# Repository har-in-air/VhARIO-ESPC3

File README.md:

# VhARIO-ESPC3 Rev B

Kicad 6 circuit schematic and PCB layout for an audio variometer using ESP32-C3 and CJMCU-117 IMU modules. The vario uses a Kalman filter to fuse acceleration data and pressure altitude data for 'zero-lag' response. You can find the [firmware project here](https://github.com/har-in-air/ESP32C3_BLUETOOTH_AUDIO_VARIO).

2-layer PCB sized for [Hammond 1551K 80x40x20 mm enclosure](docs/1551K.pdf).

Li-poly battery recharging via USB-C.

ESP32-C3 flash and debug via built-in USB serial jtag peripheral.

All SMD passive components use Kicad hand-solderable footprints.

All component symbols and footprints used in the project are in project-specific libraries in the `/libraries` folder.

## Hardware

* AI-Thinker  ESP-C3 12F module (C3FN4) with 4MByte flash.
* CJMCU-117 IMU module (MPU9250 + MS5611).
* 74HC240 used as push-pull piezo speaker driver.
* 1800mAH Li-Poly battery.
* MCP73871 battery charger @ 500mA max.
* Soft-switched power on/off via SW3.
* USB serial jtag programming and debug via USB-C interface. The flash/debug jumper can be a PCM12 slide switch (SW2) on the bottom layer if you want access from outside the enclosure. Or you can solder a 2.54mm pitch header with a jumper cap (JP1) on the top layer. The jumper is shorted only for flash/debug and is open for normal vario operation.

## Schematic
[Schematic PDF](docs/vhario-espc3-schematic.pdf)

## Differences between Rev A and Rev B hardware
* The Rev A archive can be found in the releases section.
* Rev B is a Kicad 6 project (6.0.6 as of date). Rev A was unfortunately developed with the Kicad 6.99 development branch. This is incompatible with the Kicad 6 project file format. The Rev A project can only be opened with a Kicad 6.99 development build from 2022 Jan 26 or later.
* Flash and debug in Rev B uses the ESP32-C3 built-in USB serial jtag peripheral with a jumper or slide switch (JP1/SW2). For Rev A hardware, an external USB-UART adapter and jumper/switch is required. 
* For Rev B, all smd components except for a couple of modules have been placed on one side of the PCB to facilitate automated assembly.
* For Rev B, the power/bluetooth LED and charging status LED are placed together so only one enclosure LED window is required.
* The [firmware](https://github.com/har-in-air/ESP32C3_BLUETOOTH_AUDIO_VARIO) can be configured to support either Rev A or Rev B hardware. The configuration options are in the `platformio.ini` file.

## Kicad 3D view

## Assembly

# Credits

Prototype design, component sourcing and PCB assembly in collaboration with Benoit Arnal.

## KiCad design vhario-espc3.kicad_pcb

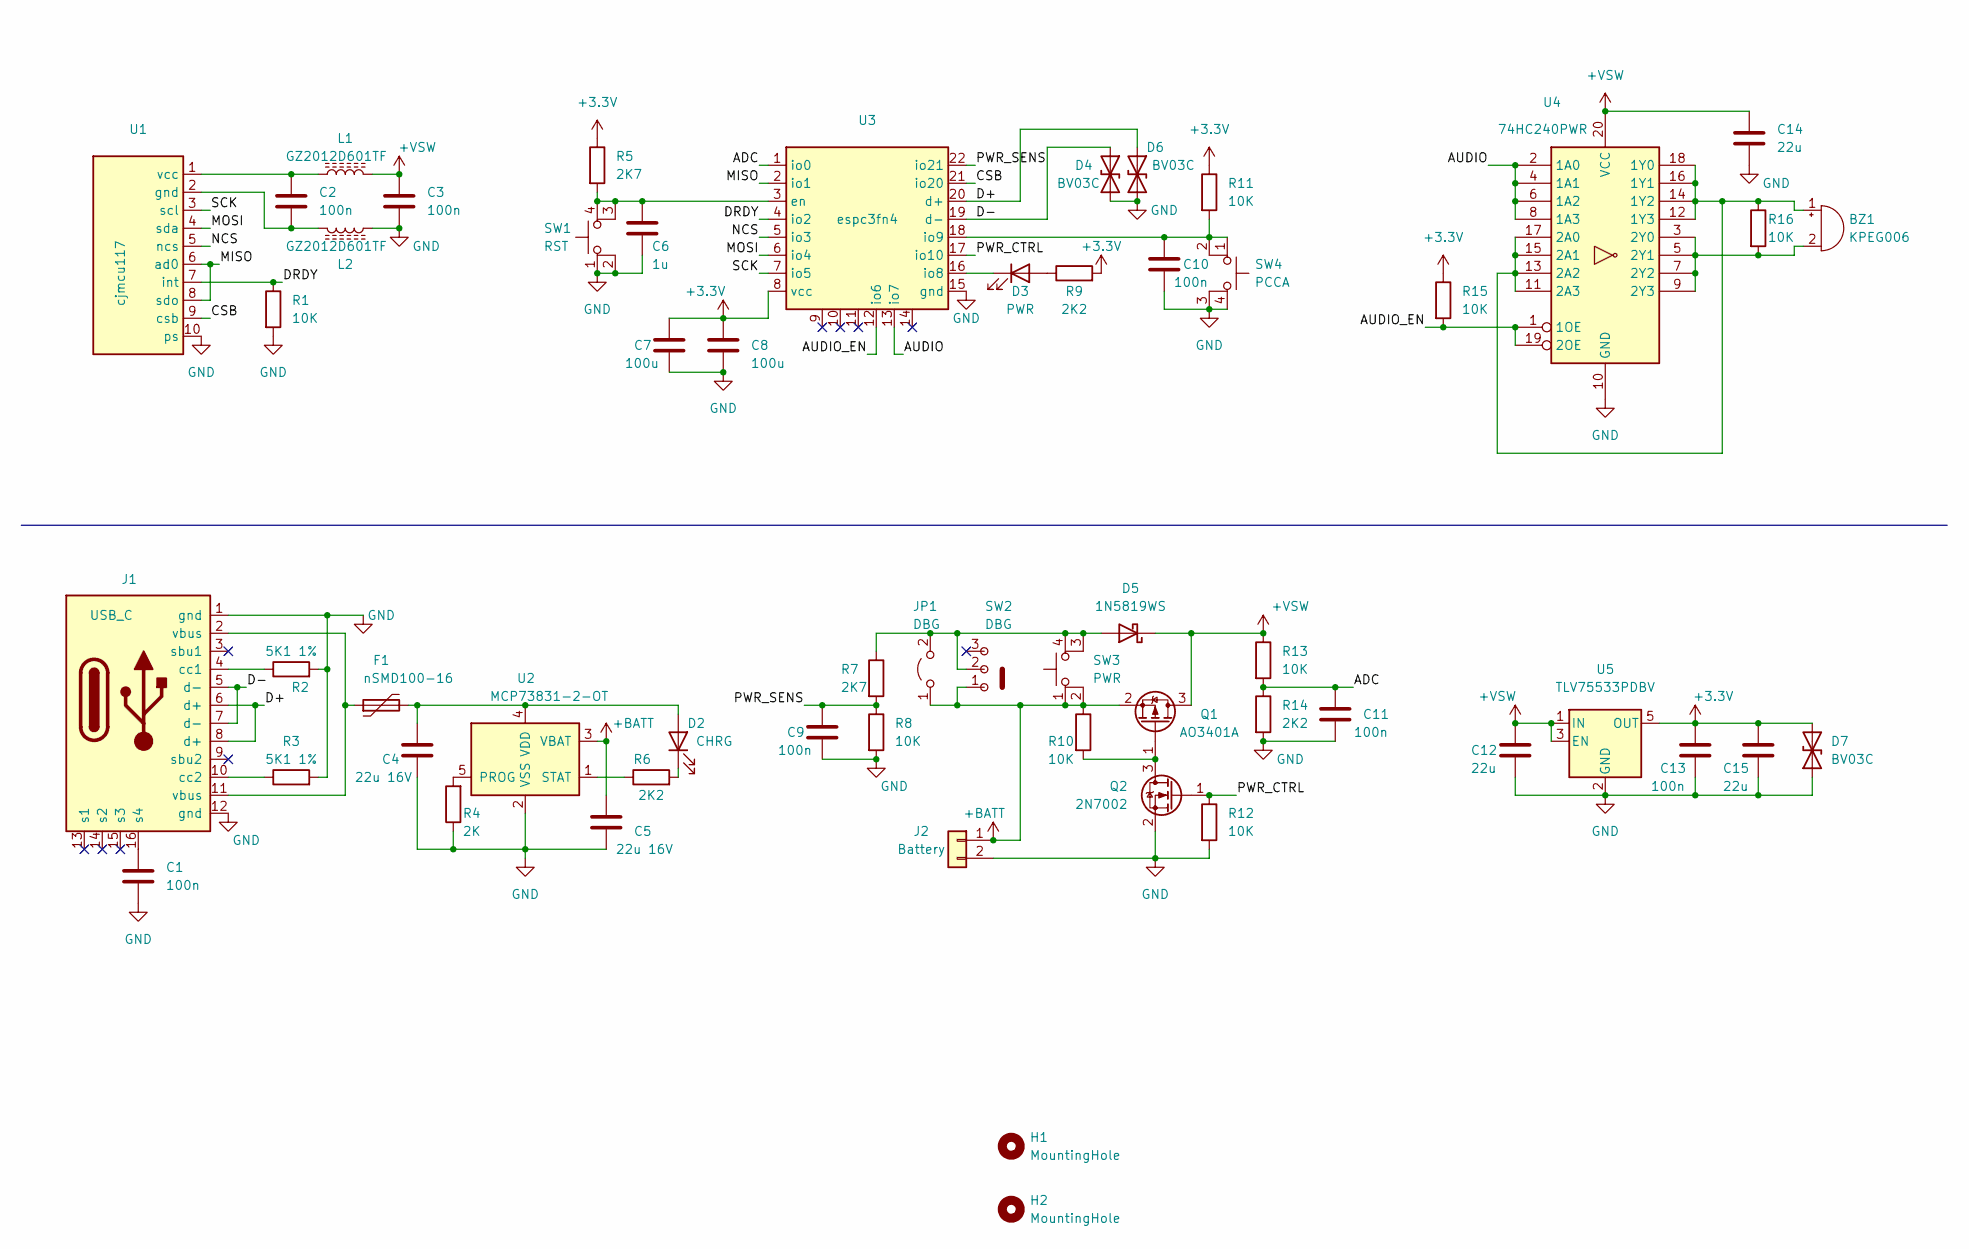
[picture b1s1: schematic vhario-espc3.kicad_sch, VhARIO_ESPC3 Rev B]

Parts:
BZ1: KPEG006; conn_smd_1x2_2mm
C1, C2, C3, C9, C10, C11, C13: 100n; C_0603_1608Metric_Pad1.08x0.95mm_HandSolder
C4, C5: 22u 16V; C_1206_3216Metric_Pad1.33x1.80mm_HandSolder
C6: 1u; C_0603_1608Metric_Pad1.08x0.95mm_HandSolder
C7, C8: 100u; C_1206_3216Metric_Pad1.33x1.80mm_HandSolder
C12, C14, C15: 22u; C_1206_3216Metric_Pad1.33x1.80mm_HandSolder
D2: CHRG; LED_0805_2012Metric_Pad1.15x1.40mm_HandSolder
D3: PWR; LED_0805_2012Metric_Pad1.15x1.40mm_HandSolder
D4, D6, D7: BV03C; D_SOD-323_HandSoldering
D5: 1N5819WS; D_SOD-323_HandSoldering
F1: nSMD100-16; Fuse_1812_4532Metric_Pad1.30x3.40mm_HandSolder
H1, H2: MountingHole; MountingHole_2.5mm
J1: USB_C; usb_c_16
J2: Battery; JST_PH_B2B-PH-K_1x02_P2.00mm_Vertical
JP1: DBG; PinSocket_1x02_P2.54mm_Vertical
L1, L2: GZ2012D601TF; L_0805_2012Metric_Pad1.15x1.40mm_HandSolder
Q1: AO3401A; SOT-23
Q2: 2N7002; SOT-23
R1, R8, R10, R11, R12, R13, R15, R16: 10K; R_0603_1608Metric_Pad0.98x0.95mm_HandSolder
R2, R3: 5K1 1%; R_0603_1608Metric_Pad0.98x0.95mm_HandSolder
R4: 2K; R_0603_1608Metric_Pad0.98x0.95mm_HandSolder
R5, R7: 2K7; R_0603_1608Metric_Pad0.98x0.95mm_HandSolder
R6: 2K2; C_0603_1608Metric_Pad1.08x0.95mm_HandSolder
R9, R14: 2K2; R_0603_1608Metric_Pad0.98x0.95mm_HandSolder
SW1: RST; smd_btn4
SW2: DBG; SW_SPDT_PCM12
SW3: PWR; smd_btn4
SW4: PCCA; smd_btn4
U1: cjmcu117
U2: MCP73831-2-OT; SOT-23-5
U3: espc3fn4
U4: 74HC240PWR; SSOP-20_4.4x6.5mm_P0.65mm
U5: TLV75533PDBV; SOT-23-5

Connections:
+3V3: C7.1, C8.1, C13.1, C15.1, D7.2 (A2), R5.1, R9.2, R11.1, R15.1, U3.8 (vcc), U5.5 (OUT)
+BATT: C5.1, J2.1, JP1.1 (A), Q1.2 (S), R10.1, SW2.1 (A), SW3.1, SW3.2, U2.3 (VBAT); also elsewhere on the board
+VSW: C3.1, C12.1, C14.1, D5.1 (K), L1.2, Q1.3 (D), R13.1, U4.20 (VCC), U5.1 (IN), U5.3 (EN)
/ADC: C11.1, R13.2, R14.1, U3.1 (io0)
/AUDIO: U3.13 (io7), U4.2 (1A0), U4.4 (1A1), U4.6 (1A2), U4.8 (1A3)
/AUDIO_EN: R15.2, U3.12 (io6), U4.1 (1OE), U4.19 (2OE)
/CSB: U1.9 (csb), U3.21 (io20)
/D+: D6.1 (A1), J1.6 (d+), J1.8 (d+), U3.20 (d+)
/D-: D4.1 (A1), J1.5 (d-), J1.7 (d-), U3.19 (d-)
/DRDY: R1.1, U1.7 (int), U3.4 (io2)
/MISO: U1.6 (ad0), U1.8 (sdo), U3.2 (io1)
/MOSI: U1.4 (sda), U3.6 (io4)
/NCS: U1.5 (ncs), U3.5 (io3)
/PWR_CTRL: Q2.1 (G), R12.1, U3.17 (io10)
/PWR_SENS: C9.1, R7.2, R8.1, U3.22 (io21)
/SCK: U1.3 (scl), U3.7 (io5)
GND: C1.2, C3.2, C4.2, C5.2, C6.2, C7.2, C8.2, C9.2, C10.2, C11.2, C12.2, C13.2, C14.2, C15.2, D4.2 (A2), D6.2 (A2), D7.1 (A1), J1.1 (gnd), J1.12 (gnd), J2.2, L2.1, Q2.2 (S), R1.2, R2.2, R3.2, R4.1, R8.2, R12.2, R14.2, SW1.1, SW1.2, SW4.3 (K), SW4.4 (A), U1.10 (ps), U2.2 (VSS), U3.15 (gnd), U4.10 (GND), U5.2 (GND); also elsewhere on the board
unnamed: BZ1.1 (-), R16.1, U4.11 (2A3), U4.12 (1Y3), U4.13 (2A2), U4.14 (1Y2), U4.15 (2A1), U4.16 (1Y1), U4.17 (2A0), U4.18 (1Y0)
unnamed: BZ1.2 (+), R16.2, U4.3 (2Y0), U4.5 (2Y1), U4.7 (2Y2), U4.9 (2Y3)
unnamed: C1.1, J1.16 (s4)
unnamed: C2.1, L1.1, U1.1 (vcc)
unnamed: C2.2, L2.2, U1.2 (gnd)
unnamed: C4.1, D2.2 (A), F1.2, U2.4 (VDD)
unnamed 23: C6.1, R5.2, SW1.3 (K), SW1.4 (A), U3.3 (en); also elsewhere on the board
unnamed 24: C10.1, R11.2, SW4.1, SW4.2, U3.18 (io9); also elsewhere on the board
unnamed: D2.1 (K), R6.2
unnamed: D3.1 (K), U3.16 (io8)
unnamed: D3.2 (A), R9.1
unnamed 28: D5.2 (A), JP1.2 (B), R7.1, SW2.2 (B), SW3.3 (K), SW3.4 (A); also elsewhere on the board
unnamed: F1.1, J1.2 (vbus), J1.11 (vbus)
unnamed: J1.4 (cc1), R2.1
unnamed: J1.10 (cc2), R3.1
unnamed: Q1.1 (G), Q2.3 (D), R10.2
unnamed: R4.2, U2.5 (PROG)
unnamed: R6.1, U2.1 (STAT)

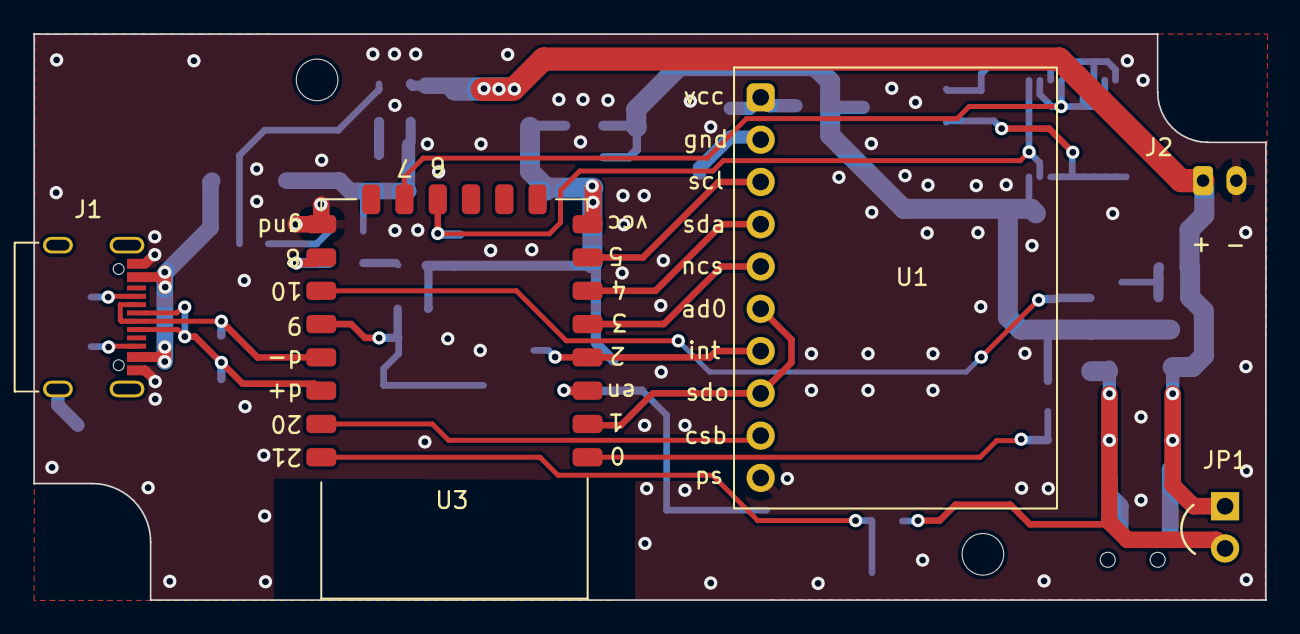
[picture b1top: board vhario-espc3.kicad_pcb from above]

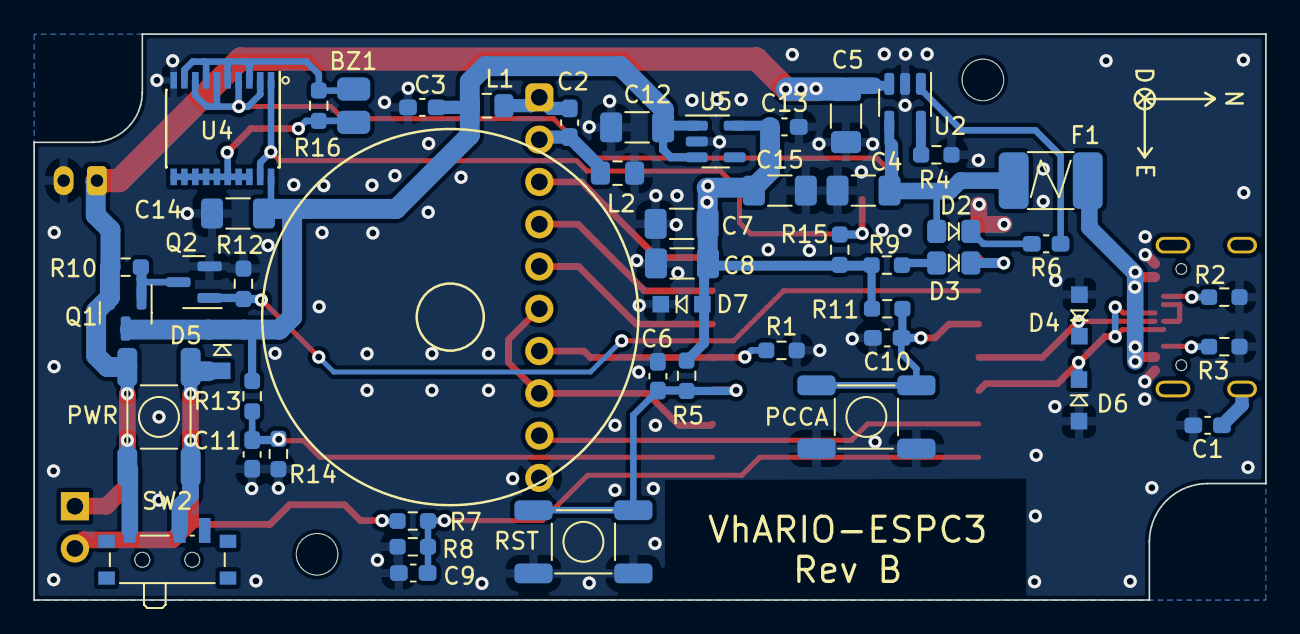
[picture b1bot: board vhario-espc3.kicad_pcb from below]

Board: 2 copper layers, 74.0 x 34.0 mm, 57 parts (50 on the bottom side), 35 nets.

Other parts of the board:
PCCA: PCCA; smd_btn4
PWR: PWR; smd_btn4
RST: RST; smd_btn4

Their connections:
+BATT: PWR.1, PWR.2; also elsewhere on the board
GND: PCCA.3 (K), PCCA.4 (A), RST.1, RST.2; also elsewhere on the board
unnamed 23: RST.3 (K), RST.4 (A); also elsewhere on the board
unnamed 24: PCCA.1, PCCA.2; also elsewhere on the board
unnamed 28: PWR.3 (K), PWR.4 (A); also elsewhere on the board

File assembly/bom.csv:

Designator,Footprint,Quantity,Value,LCSC Part #
H2,MountingHole_2.5mm,1,MountingHole,
U1,cjmcu117,1,cjmcu117,
H1,MountingHole_2.5mm,1,MountingHole,
J1,usb_c_16,1,USB_C,
U3,espc3fn4,1,espc3fn4,
J2,JST_PH_B2B-PH-K_1x02_P2.00mm_Vertical,1,Battery,
JP1,PinSocket_1x02_P2.54mm_Vertical,1,DBG,
F1,Fuse_1812_4532Metric_Pad1.30x3.40mm_HandSolder,1,nSMD100-16,
D6,D_SOD-323_HandSoldering,1,BV03C,
D4,D_SOD-323_HandSoldering,1,BV03C,
C1,C_0603_1608Metric_Pad1.08x0.95mm_HandSolder,1,100n,
R11,R_0603_1608Metric_Pad0.98x0.95mm_HandSolder,1,10K,
Q2,SOT-23,1,2N7002,
R5,R_0603_1608Metric_Pad0.98x0.95mm_HandSolder,1,2K7,
SW2,SW_SPDT_PCM12,1,DBG,
L2,L_0805_2012Metric_Pad1.15x1.40mm_HandSolder,1,GZ2012D601TF,
D2,LED_0805_2012Metric_Pad1.15x1.40mm_HandSolder,1,CHRG,
BZ1,conn_smd_1x2_2mm,1,KPEG006,
C12,C_1206_3216Metric_Pad1.33x1.80mm_HandSolder,1,22u,
C13,C_0603_1608Metric_Pad1.08x0.95mm_HandSolder,1,100n,
R2,R_0603_1608Metric_Pad0.98x0.95mm_HandSolder,1,5K1 1%,
C15,C_1206_3216Metric_Pad1.33x1.80mm_HandSolder,1,22u,
U2,SOT-23-5,1,MCP73831-2-OT,
R16,R_0603_1608Metric_Pad0.98x0.95mm_HandSolder,1,10K,
L1,L_0805_2012Metric_Pad1.15x1.40mm_HandSolder,1,GZ2012D601TF,
C3,C_0603_1608Metric_Pad1.08x0.95mm_HandSolder,1,100n,
U5,SOT-23-5,1,TLV75533PDBV,
C6,C_0603_1608Metric_Pad1.08x0.95mm_HandSolder,1,1u,
PWR,smd_btn4,1,PWR,
C2,C_0603_1608Metric_Pad1.08x0.95mm_HandSolder,1,100n,
PCCA,smd_btn4,1,PCCA,
R8,R_0603_1608Metric_Pad0.98x0.95mm_HandSolder,1,10K,
RST,smd_btn4,1,RST,
R12,R_0603_1608Metric_Pad0.98x0.95mm_HandSolder,1,10K,
R14,R_0603_1608Metric_Pad0.98x0.95mm_HandSolder,1,2K2,
R1,R_0603_1608Metric_Pad0.98x0.95mm_HandSolder,1,10K,
D5,D_SOD-323_HandSoldering,1,1N5819WS,
C4,C_1206_3216Metric_Pad1.33x1.80mm_HandSolder,1,22u 16V,
C11,C_0603_1608Metric_Pad1.08x0.95mm_HandSolder,1,100n,
R6,C_0603_1608Metric_Pad1.08x0.95mm_HandSolder,1,2K2,
R4,R_0603_1608Metric_Pad0.98x0.95mm_HandSolder,1,2K,
R3,R_0603_1608Metric_Pad0.98x0.95mm_HandSolder,1,5K1 1%,
R15,R_0603_1608Metric_Pad0.98x0.95mm_HandSolder,1,10K,
D7,D_SOD-323_HandSoldering,1,BV03C,
C5,C_1206_3216Metric_Pad1.33x1.80mm_HandSolder,1,22u 16V,
Q1,SOT-23,1,AO3401A,
R9,R_0603_1608Metric_Pad0.98x0.95mm_HandSolder,1,2K2,
D3,LED_0805_2012Metric_Pad1.15x1.40mm_HandSolder,1,PWR,
C10,C_0603_1608Metric_Pad1.08x0.95mm_HandSolder,1,100n,
R10,R_0603_1608Metric_Pad0.98x0.95mm_HandSolder,1,10K,
R7,R_0603_1608Metric_Pad0.98x0.95mm_HandSolder,1,2K7,
C14,C_1206_3216Metric_Pad1.33x1.80mm_HandSolder,1,22u,
C8,C_1206_3216Metric_Pad1.33x1.80mm_HandSolder,1,100u,
C7,C_1206_3216Metric_Pad1.33x1.80mm_HandSolder,1,100u,
R13,R_0603_1608Metric_Pad0.98x0.95mm_HandSolder,1,10K,
U4,SSOP-20_4.4x6.5mm_P0.65mm,1,74HC240PWR,
C9,C_0603_1608Metric_Pad1.08x0.95mm_HandSolder,1,100n,

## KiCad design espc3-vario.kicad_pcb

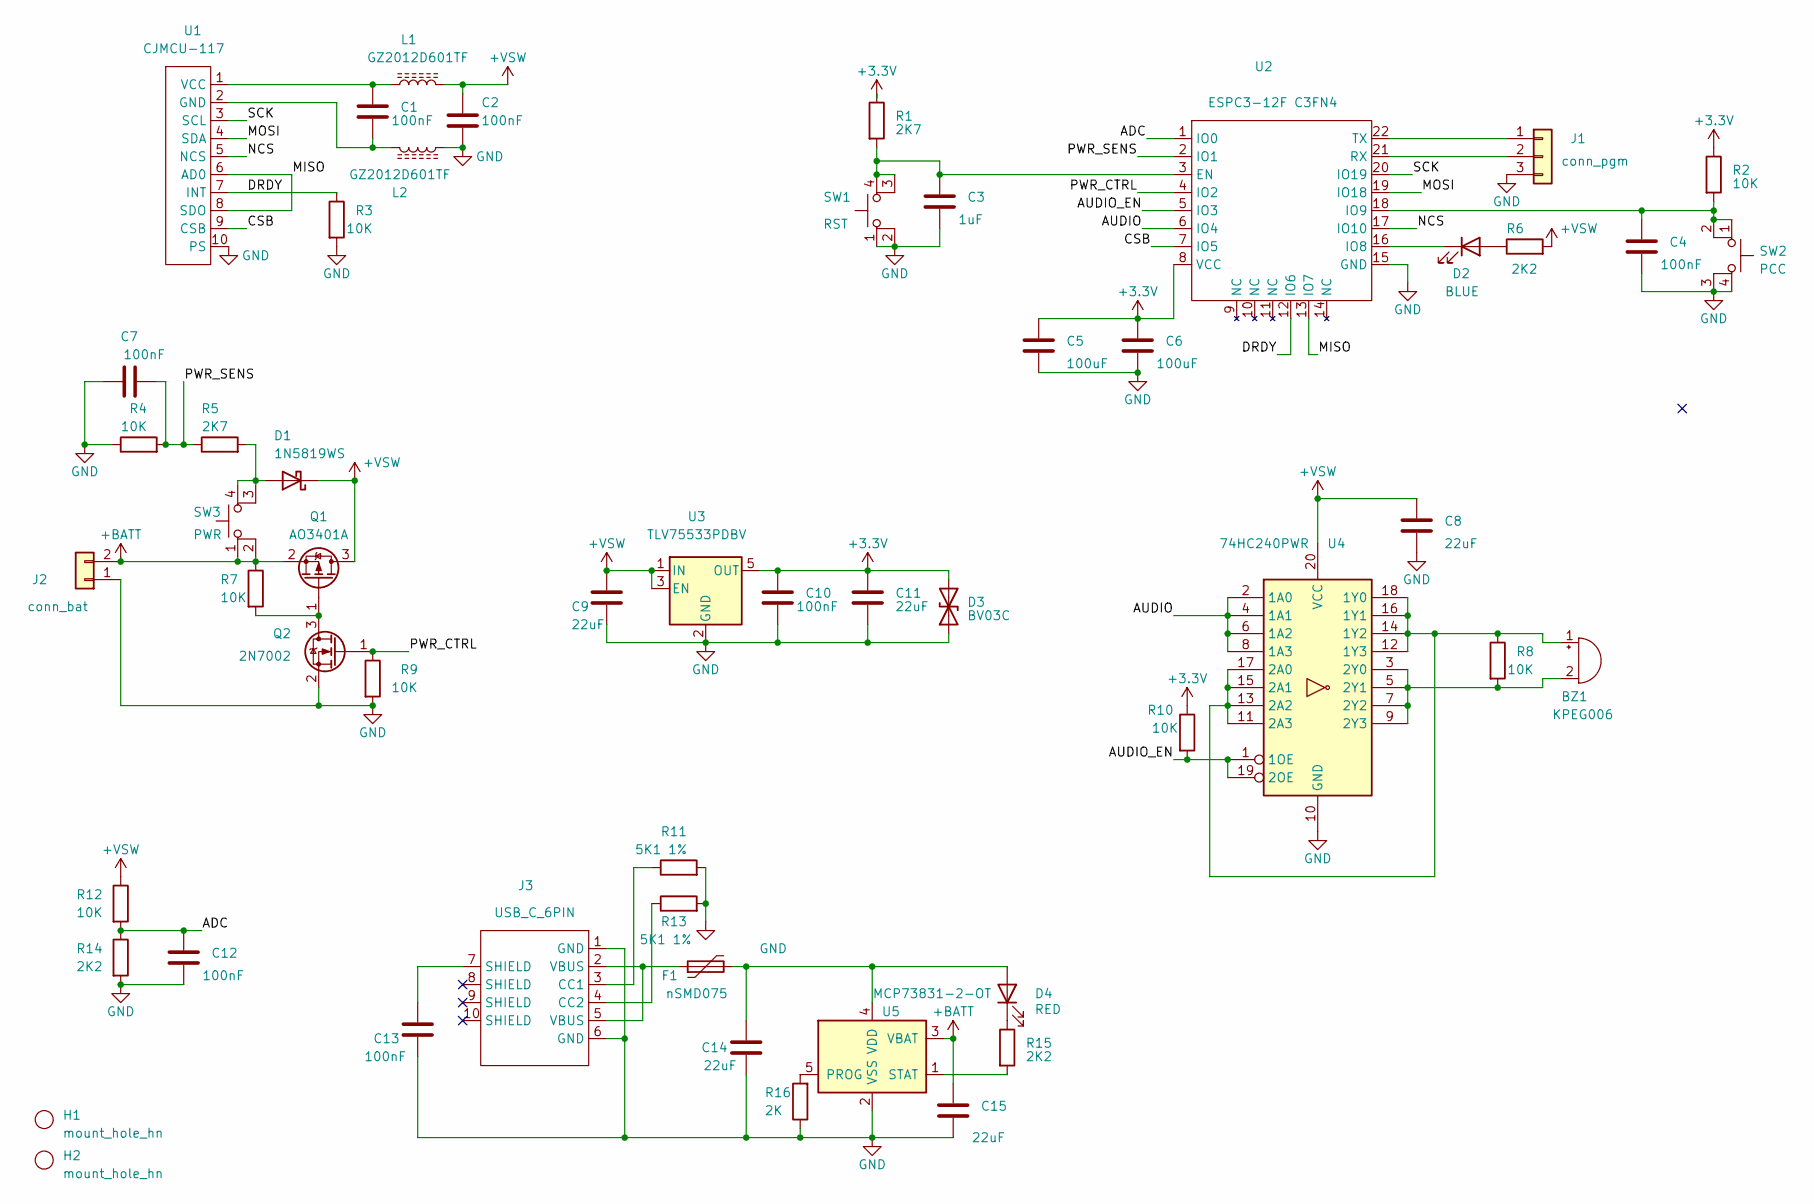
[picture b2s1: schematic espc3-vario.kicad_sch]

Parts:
BZ1: KPEG006; smd_conn2_hn
C1, C2, C4, C7, C10, C12, C13: 100nF; C_0805_2012Metric_Pad1.18x1.45mm_HandSolder; LCSC C49678
C3: 1uF; C_0805_2012Metric_Pad1.18x1.45mm_HandSolder; LCSC C28323
C5, C6: 100uF; C_1206_3216Metric_Pad1.33x1.80mm_HandSolder; LCSC C15008
C8, C9, C11, C14, C15: 22uF; C_1206_3216Metric_Pad1.33x1.80mm_HandSolder; LCSC C5672
D1: 1N5819WS; D_SOD-323_HandSoldering; LCSC C191023
D2: BLUE; LED_0805_2012Metric_Pad1.15x1.40mm_HandSolder; LCSC C189307
D3: BV03C; D_SOD-323_HandSoldering; LCSC C51125
D4: RED; LED_0805_2012Metric_Pad1.15x1.40mm_HandSolder; LCSC C138549
F1: nSMD075; Fuse_1206_3216Metric_Pad1.42x1.75mm_HandSolder; LCSC C70078
H1, H2: mount_hole_hn; MountingHole_2.5mm
J1: conn_pgm; pgm_conn_hn
J2: conn_bat; smd_conn2_hn
J3: USB_C_6PIN; usbc_6pin_hn
L1, L2: GZ2012D601TF; L_0805_2012Metric_Pad1.15x1.40mm_HandSolder; LCSC C1017
Q1: AO3401A; SOT-23_Handsoldering; LCSC C15127
Q2: 2N7002; SOT-23_Handsoldering; LCSC C8545
R1, R5: 2K7; R_0805_2012Metric_Pad1.20x1.40mm_HandSolder; LCSC C17530
R2, R3, R4, R7, R8, R9, R10, R12: 10K; R_0805_2012Metric_Pad1.20x1.40mm_HandSolder; LCSC C17724
R6, R14, R15: 2K2; R_0805_2012Metric_Pad1.20x1.40mm_HandSolder; LCSC C17520
R11, R13: 5K1 1%; R_0805_2012Metric_Pad1.20x1.40mm_HandSolder; LCSC C27834
R16: 2K; R_0805_2012Metric_Pad1.20x1.40mm_HandSolder; LCSC C17604
SW1: RST; smd_btn4_hn
SW2: PCC; smd_btn4_hn
SW3: PWR; smd_btn4_hn
U1: CJMCU-117; cjmcu_117_hn
U2: ESPC3-12F C3FN4; espc3fn4_hn
U3: TLV75533PDBV; SOT-23-5_HandSoldering; LCSC C404027
U4: 74HC240PWR; SSOP-20_4.4x6.5mm_P0.65mm; LCSC C470968
U5: MCP73831-2-OT; SOT-23-5_HandSoldering; LCSC C424093

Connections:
+3V3: C5.1, C6.1, C10.1, C11.1, D3.2 (A2), R1.1, R2.1, R10.1, U2.8 (VCC), U3.5 (OUT)
+BATT: C15.1, J2.2, Q1.2 (S), R7.1, SW3.1, SW3.2, U5.3 (VBAT)
+VSW: C2.1, C8.1, C9.1, D1.1 (K), L1.2, Q1.3 (D), R6.2, R12.1, U3.1 (IN), U3.3 (EN), U4.20 (VCC)
/ADC: C12.1, R12.2, R14.1, U2.1 (IO0)
/AUDIO: U2.6 (IO4), U4.2 (1A0), U4.4 (1A1), U4.6 (1A2), U4.8 (1A3)
/AUDIO_EN: R10.2, U2.5 (IO3), U4.1 (1OE), U4.19 (2OE)
/CSB: U1.9 (CSB), U2.7 (IO5)
/DRDY: R3.1, U1.7 (INT), U2.12 (IO6)
/MISO: U1.6 (AD0), U1.8 (SDO), U2.13 (IO7)
/MOSI: U1.4 (SDA), U2.19 (IO18)
/NCS: U1.5 (NCS), U2.17 (IO10)
/PWR_CTRL: Q2.1 (G), R9.1, U2.4 (IO2)
/PWR_SENS: C7.2, R4.2, R5.1, U2.2 (IO1)
/SCK: U1.3 (SCL), U2.20 (IO19)
GND: C2.2, C3.2, C4.2, C5.2, C6.2, C7.1, C8.2, C9.2, C10.2, C11.2, C12.2, C13.2, C14.2, C15.2, D3.1 (A1), J1.3, J2.1, J3.1 (GND), J3.6 (GND), L2.1, Q2.2 (S), R3.2, R4.1, R9.2, R11.2, R13.2, R14.2, R16.1, SW1.1, SW1.2, SW2.3 (K), SW2.4 (A), U1.10 (PS), U2.15 (GND), U3.2 (GND), U4.10 (GND), U5.2 (VSS)
unnamed: BZ1.2 (+), R8.2, U4.3 (2Y0), U4.5 (2Y1), U4.7 (2Y2), U4.9 (2Y3)
unnamed: BZ1.1 (-), R8.1, U4.11 (2A3), U4.12 (1Y3), U4.13 (2A2), U4.14 (1Y2), U4.15 (2A1), U4.16 (1Y1), U4.17 (2A0), U4.18 (1Y0)
unnamed: D1.2 (A), R5.2, SW3.3 (K), SW3.4 (A)
unnamed: D2.2 (A), R6.1
unnamed: D2.1 (K), U2.16 (IO8)
unnamed: C14.1, D4.2 (A), F1.2, U5.4 (VDD)
unnamed: D4.1 (K), R15.1
unnamed: J1.1, U2.22 (TX)
unnamed: J1.2, U2.21 (RX)
unnamed: J3.3 (CC1), R11.1
unnamed: J3.4 (CC2), R13.1
unnamed: C13.1, J3.7 (SHIELD)
unnamed: F1.1, J3.2 (VBUS), J3.5 (VBUS)
unnamed: Q1.1 (G), Q2.3 (D), R7.2
unnamed: C3.1, R1.2, SW1.3 (K), SW1.4 (A), U2.3 (EN)
unnamed: C1.2, L2.2, U1.2 (GND)
unnamed: C1.1, L1.1, U1.1 (VCC)
unnamed: C4.1, R2.2, SW2.1, SW2.2, U2.18 (IO9)
unnamed: R16.2, U5.5 (PROG)
unnamed: R15.2, U5.1 (STAT)

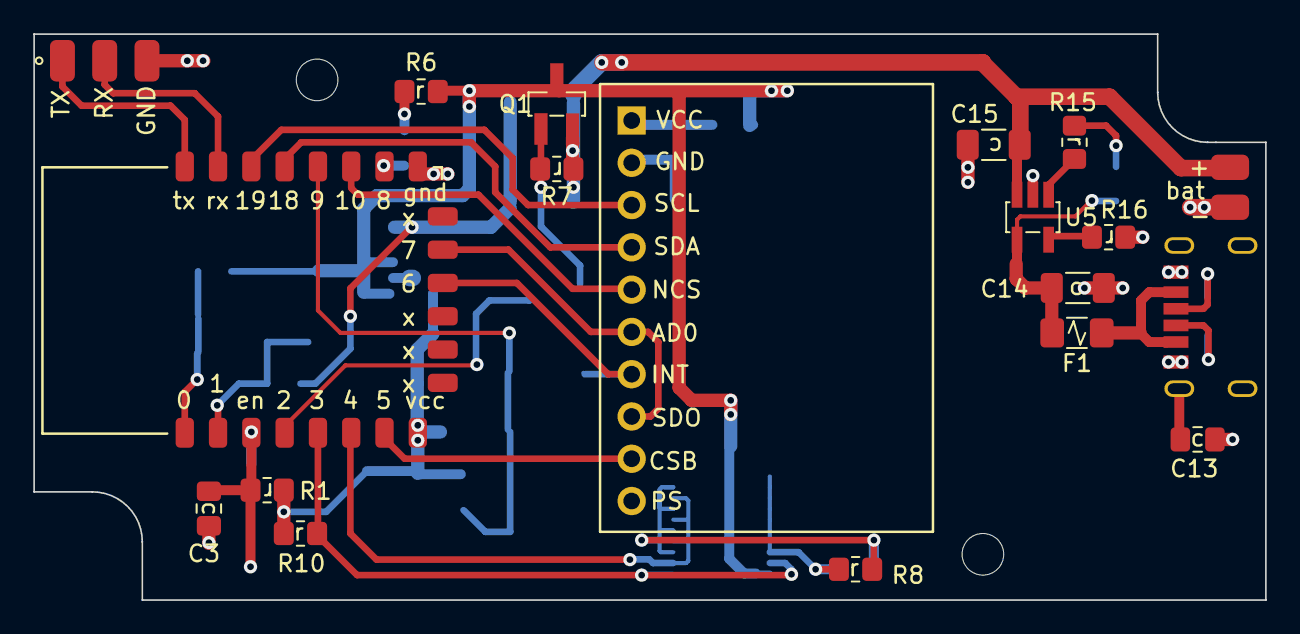
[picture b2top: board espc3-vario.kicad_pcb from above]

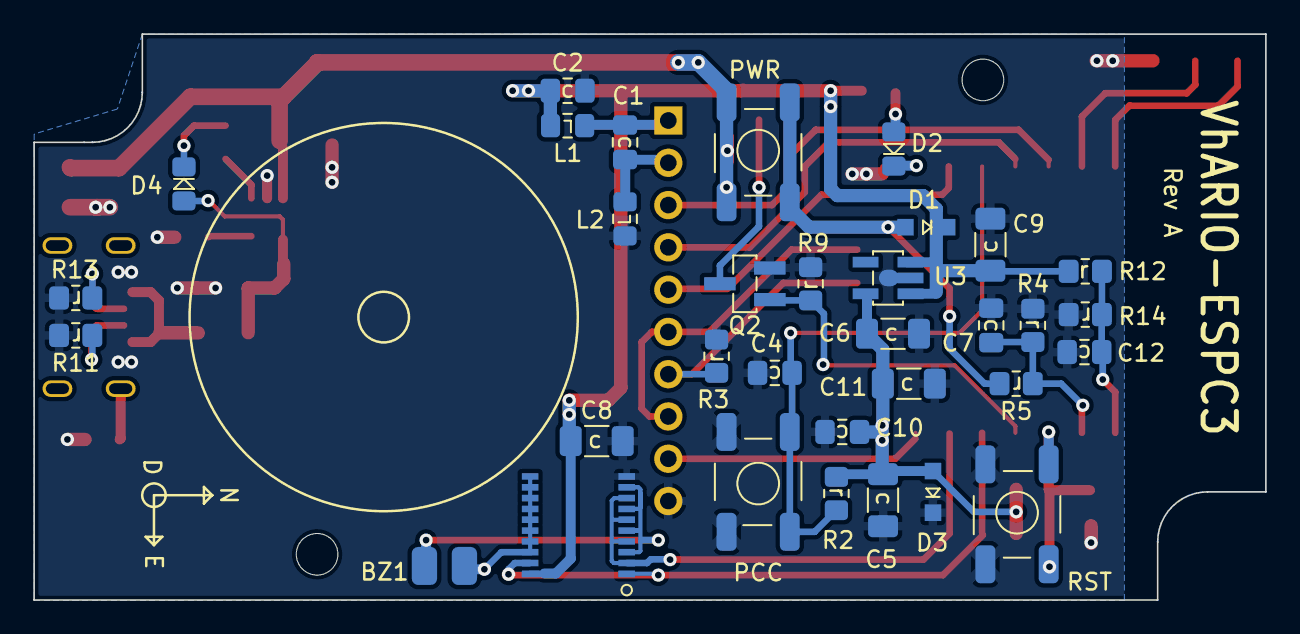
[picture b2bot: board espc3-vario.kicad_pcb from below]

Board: 2 copper layers, 74.0 x 34.0 mm, 54 parts (33 on the bottom side), 35 nets.

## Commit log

2022-03-11 regenerate
2022-03-12 update schematic pdf
2022-03-12 optimize track widths
2022-03-15 no via in pads, add silkscreen outlines
2022-03-15 add 2d layout screenshots
2022-03-28 add pcba images
2022-05-07 change fuse to 1A
2022-05-07 change fuse
2022-06-29 Rev B commit (see README for changes)
2022-06-29 add usb c connector datasheet
2022-06-29 remove backups folder
2022-06-29 update footprints
2022-06-30 change flash/dbg jumper options
2022-06-30 update schematic
2022-06-30 increase keepout area
2022-06-30 annotate piezo coords
2022-07-01 move via out of pad
2022-07-03 optimize tracks
2022-08-17 move via out of pad, cleanup silkscreen
2022-09-11 remove old images
2024-05-14 Create LICENSE
